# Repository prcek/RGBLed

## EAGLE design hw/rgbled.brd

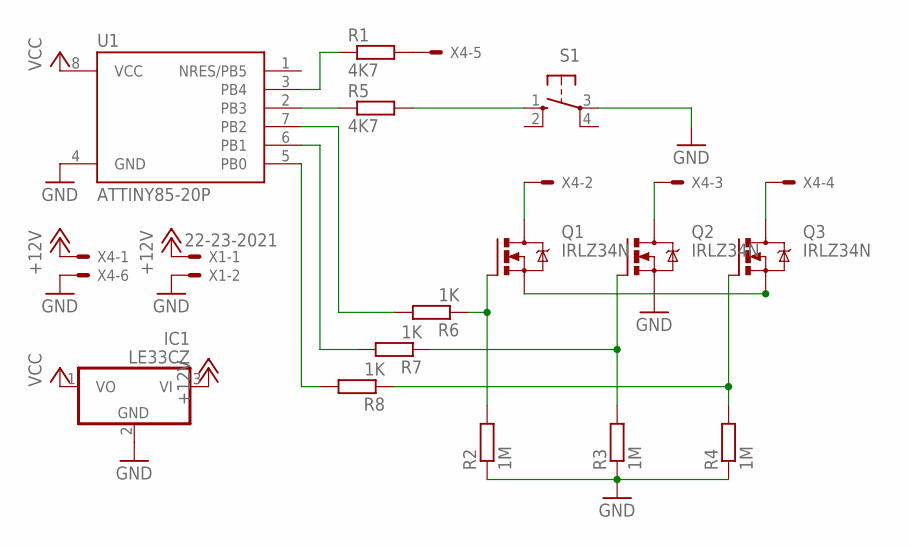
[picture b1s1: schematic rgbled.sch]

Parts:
IC1: LE33CZ; TO92
Q1, Q2, Q3: IRLZ34N; TO220BV
R1, R5: 4K7; 0204/5
R2, R3, R4: 1M; 0204/5
R6, R7, R8: 1K; 0204/5
S1: 10-XX; B3F-10XX
U1: ATTINY85-20P; PDIP08_300MIL
X1: 22-23-2021
X4: 22-23-2061

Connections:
+12V: IC1.3 (VI), X1.1, X4.1
GND: IC1.2 (GND), Q1.S, Q2.S, Q3.S, R2.1, R3.1, R4.1, S1.3, U1.4 (GND), X1.2, X4.6
unnamed: R5.2, S1.1 (S)
unnamed: Q1.D, X4.2
unnamed: Q2.D, X4.3
unnamed: Q3.D, X4.4
unnamed: R1.1, U1.3 (PB4)
unnamed: Q1.G, R2.2, R6.1
unnamed: Q2.G, R3.2, R7.1
unnamed: Q3.G, R4.2, R8.1
unnamed: R8.2, U1.5 (PB0)
unnamed: R7.2, U1.6 (PB1)
unnamed: R6.2, U1.7 (PB2)
unnamed: R1.2, X4.5
unnamed: R5.1, U1.2 (PB3)
VCC: IC1.1 (VO), U1.8 (VCC)

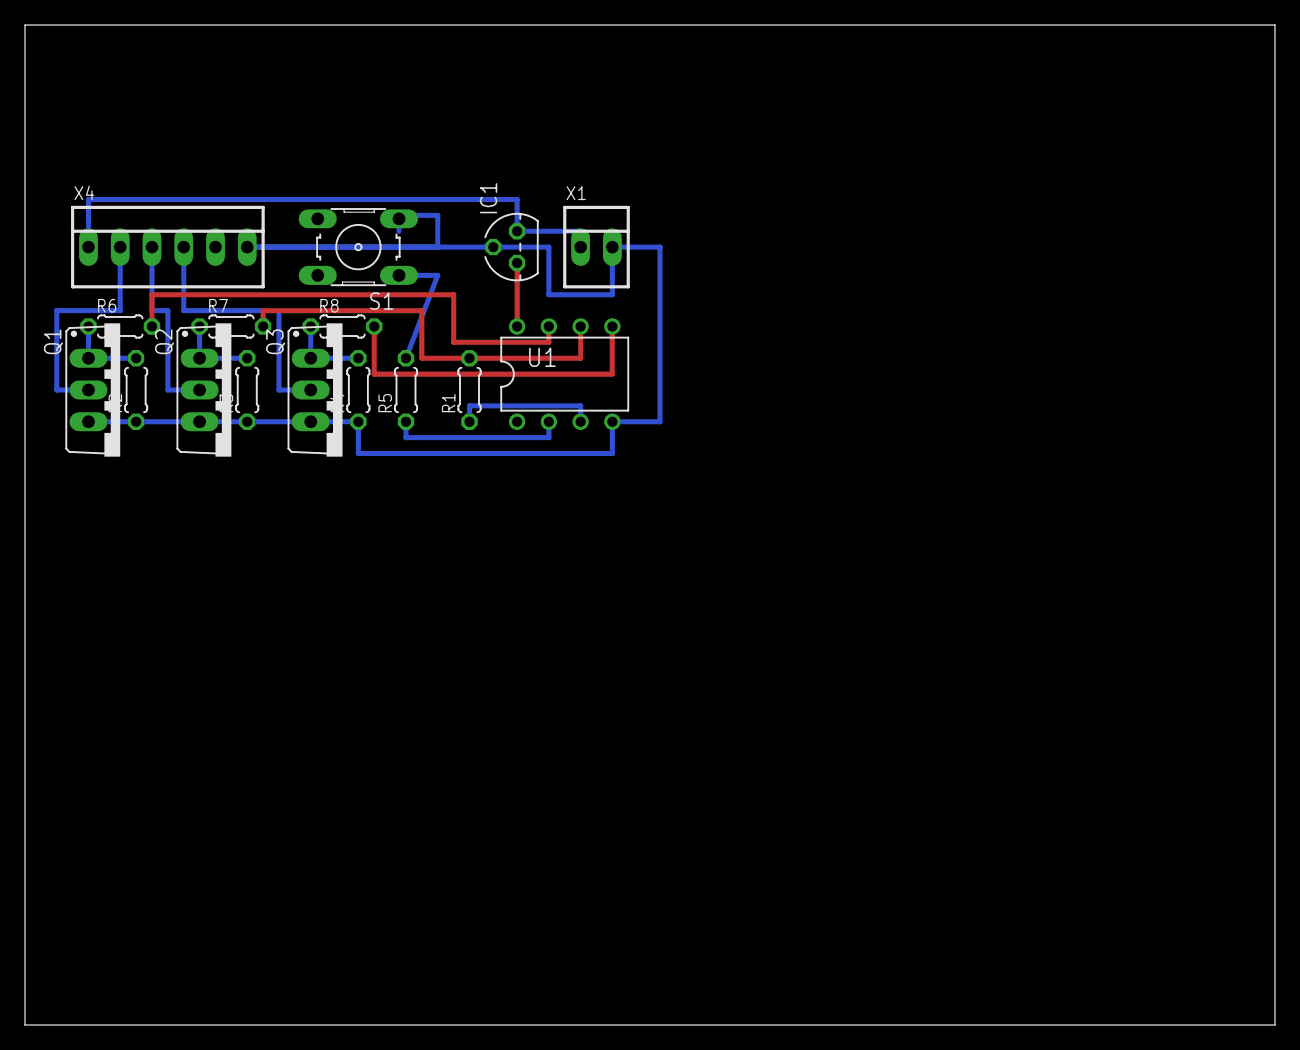
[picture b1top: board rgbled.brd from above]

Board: 2 copper layers, 100.0 x 80.0 mm, 16 parts (0 on the bottom side), 16 nets.

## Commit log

2013-10-26 sch a brd
2013-10-26 v1 boardu
2013-10-27 zapnuti led
2013-10-27 upravy sch
2013-10-28 capsense s kalibraci
2013-10-29 interupt blink test
2013-10-30 rgb drive test
2013-10-31 upravy problikavani
2014-01-05 vyhozen dotykovy senzor
